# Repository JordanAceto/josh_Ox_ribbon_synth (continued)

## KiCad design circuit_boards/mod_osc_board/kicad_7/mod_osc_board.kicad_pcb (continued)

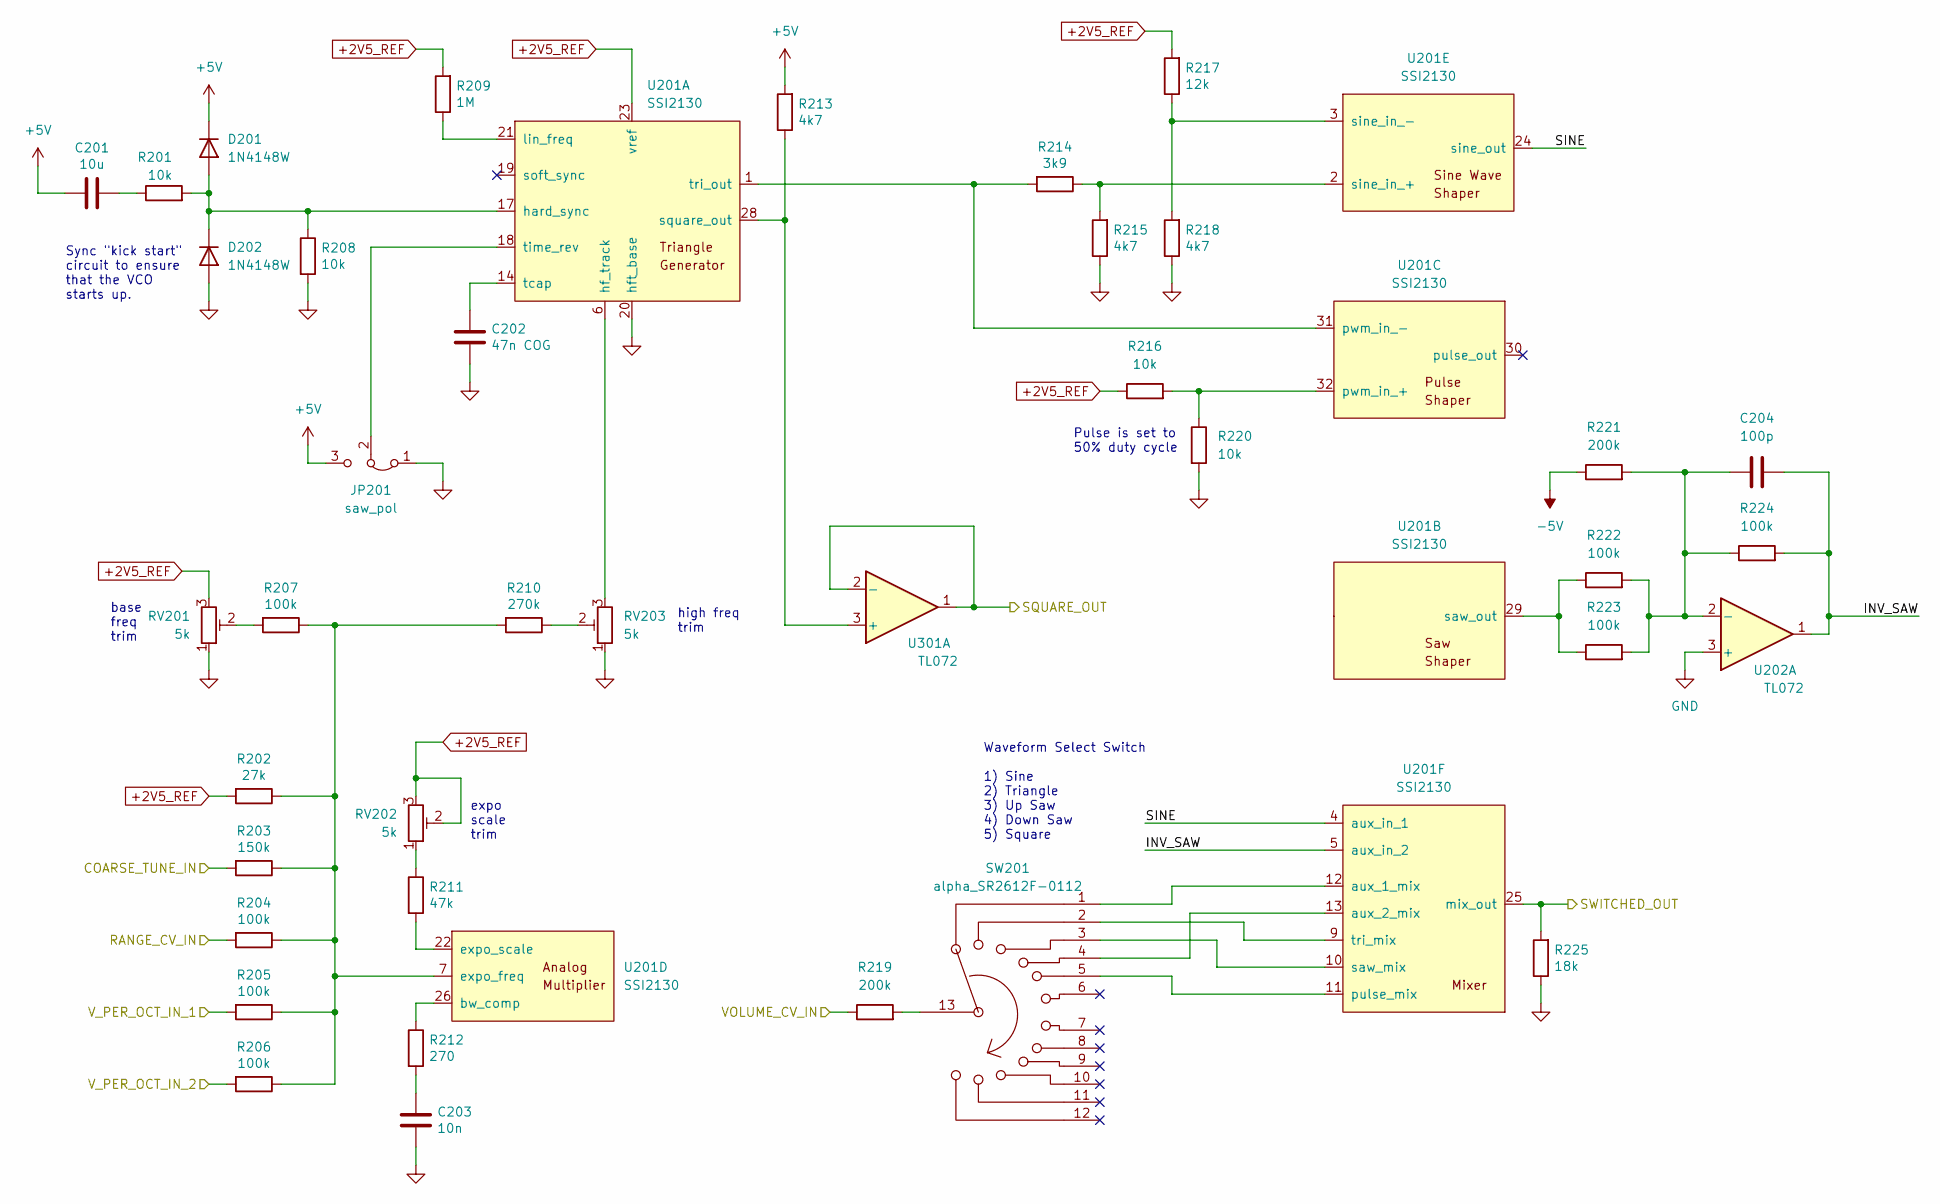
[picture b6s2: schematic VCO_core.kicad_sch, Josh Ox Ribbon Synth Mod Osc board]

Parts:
C201: 10u; C_0805_2012Metric
C202: 47n COG; C_0805_2012Metric
C203: 10n; C_0805_2012Metric
C204: 100p; C_0805_2012Metric
D201, D202: 1N4148W; D_SOD-123
JP201: saw_pol; SolderJumper-3_P1.3mm_Bridged12_RoundedPad1.0x1.5mm
R201, R208, R216, R220: 10k; R_0805_2012Metric
R202: 27k; R_0805_2012Metric
R203: 150k; R_0805_2012Metric
R204, R205, R206, R207, R222, R223, R224: 100k; R_0805_2012Metric
R209: 1M; R_0805_2012Metric
R210: 270k; R_0805_2012Metric
R211: 47k; R_0805_2012Metric
R212: 270; R_0805_2012Metric
R213, R215, R218: 4k7; R_0805_2012Metric
R214: 3k9; R_0805_2012Metric
R217: 12k; R_0805_2012Metric
R219, R221: 200k; R_0805_2012Metric
R225: 18k; R_0805_2012Metric
RV201, RV202, RV203: 5k; Potentiometer_Bourns_3296W_Vertical
SW201: alpha_SR2612F-0112; apha_SR2612F-0112
U201: SSI2130; PQN32_HandSoldering
U202, U301: TL072; SO-8_5.3x6.2mm_P1.27mm

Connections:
+2V5_REF: R202.2, R209.2, R216.1, R217.2, RV201.3, RV202.2, RV202.3, U201.23 (vref); also elsewhere on the board
+5V: C201.2, D201.1 (K), JP201.3 (B), R213.2; also elsewhere on the board
-5V: R221.1; also elsewhere on the board
/VCO_core/COARSE_TUNE_IN: R203.2; also elsewhere on the board
/VCO_core/INV_SAW: C204.2, R224.2, U201.5 (aux_in_2), U202.1
/VCO_core/RANGE_CV_IN: R204.2; also elsewhere on the board
/VCO_core/SINE: U201.4 (aux_in_1), U201.24 (sine_out)
/VCO_core/SQUARE_OUT: U301.1, U301.2 (-); also elsewhere on the board
/VCO_core/SWITCHED_OUT: R225.2, U201.25 (mix_out); also elsewhere on the board
/VCO_core/VOLUME_CV_IN: R219.1; also elsewhere on the board
/VCO_core/V_PER_OCT_IN_1: R205.2; also elsewhere on the board
/VCO_core/V_PER_OCT_IN_2: R206.2; also elsewhere on the board
unnamed: C201.1, R201.1
unnamed: C203.1, R212.2
unnamed: D201.2 (A), D202.1 (K), R201.2, R208.1, U201.17 (hard_sync)
unnamed: JP201.2 (C), U201.18 (time_rev)
unnamed: R207.2, RV201.2
unnamed: R210.1, RV203.2
unnamed: R211.1, RV202.1
unnamed: R219.2, SW201.13
unnamed: RV203.3, U201.6 (hf_track)
unnamed: R209.1, U201.21 (lin_freq)
unnamed: R213.1, U201.28 (square_out), U301.3 (+)
unnamed: C202.1, U201.14 (tcap)
unnamed: R214.2, U201.1 (tri_out), U201.31 (pwm_in_-)
unnamed: R222.1, R223.1, U201.29 (saw_out)
unnamed: R216.2, R220.1, U201.32 (pwm_in_+)
unnamed: R212.1, U201.26 (bw_comp)
unnamed: R202.1, R203.1, R204.1, R205.1, R206.1, R207.1, R210.2, U201.7 (expo_freq)
unnamed: R211.2, U201.22 (expo_scale)
unnamed: R214.1, R215.2, U201.2 (sine_in_+)
unnamed: R217.1, R218.2, U201.3 (sine_in_-)
unnamed: SW201.1, U201.12 (aux_1_mix)
unnamed: SW201.4, U201.13 (aux_2_mix)
unnamed: SW201.5, U201.11 (pulse_mix)
unnamed: SW201.3, U201.10 (saw_mix)
unnamed: SW201.2, U201.9 (tri_mix)
unnamed: C204.1, R221.2, R222.2, R223.2, R224.1, U202.2 (-)

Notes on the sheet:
Waveform Select Switch 1) Sine 2) Triangle 3) Up Saw 4) Down Saw 5) Square
high freq trim
Pulse is set to 50% duty cycle
expo scale trim
Sync "kick start" circuit to ensure that the VCO starts up.
base freq trim

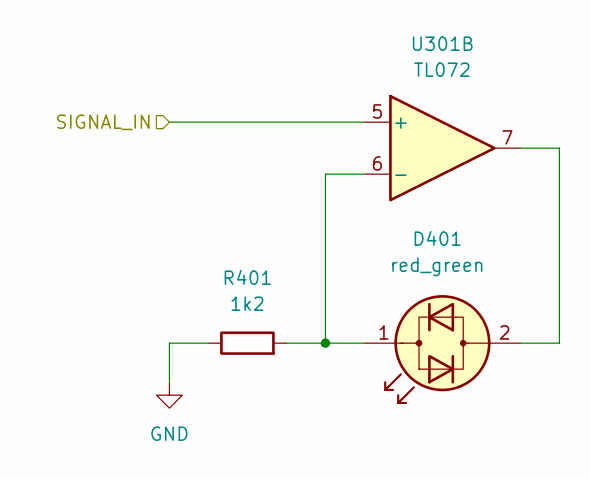
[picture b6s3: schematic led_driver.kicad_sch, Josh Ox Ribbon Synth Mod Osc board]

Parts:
D401: red_green; LED_D5.0mm
R401: 1k2; R_0805_2012Metric
U301: TL072; SO-8_5.3x6.2mm_P1.27mm

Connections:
/MOD_OSC_OUT: U301.5 (+); also elsewhere on the board
unnamed 19: D401.2 (AK), U301.7; also elsewhere on the board
unnamed 20: D401.1 (KA), R401.2, U301.6 (-); also elsewhere on the board

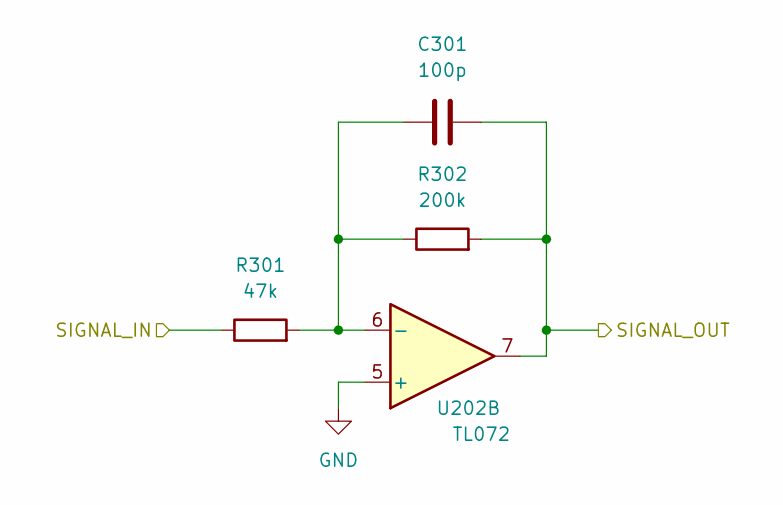
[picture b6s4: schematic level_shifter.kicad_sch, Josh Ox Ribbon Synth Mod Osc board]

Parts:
C301: 100p; C_0805_2012Metric
R301: 47k; R_0805_2012Metric
R302: 200k; R_0805_2012Metric
U202: TL072; SO-8_5.3x6.2mm_P1.27mm

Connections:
/MOD_OSC_OUT: C301.2, R302.2, U202.7; also elsewhere on the board
/VCO_core/SWITCHED_OUT: R301.1; also elsewhere on the board
unnamed: C301.1, R301.2, R302.1, U202.6 (-)

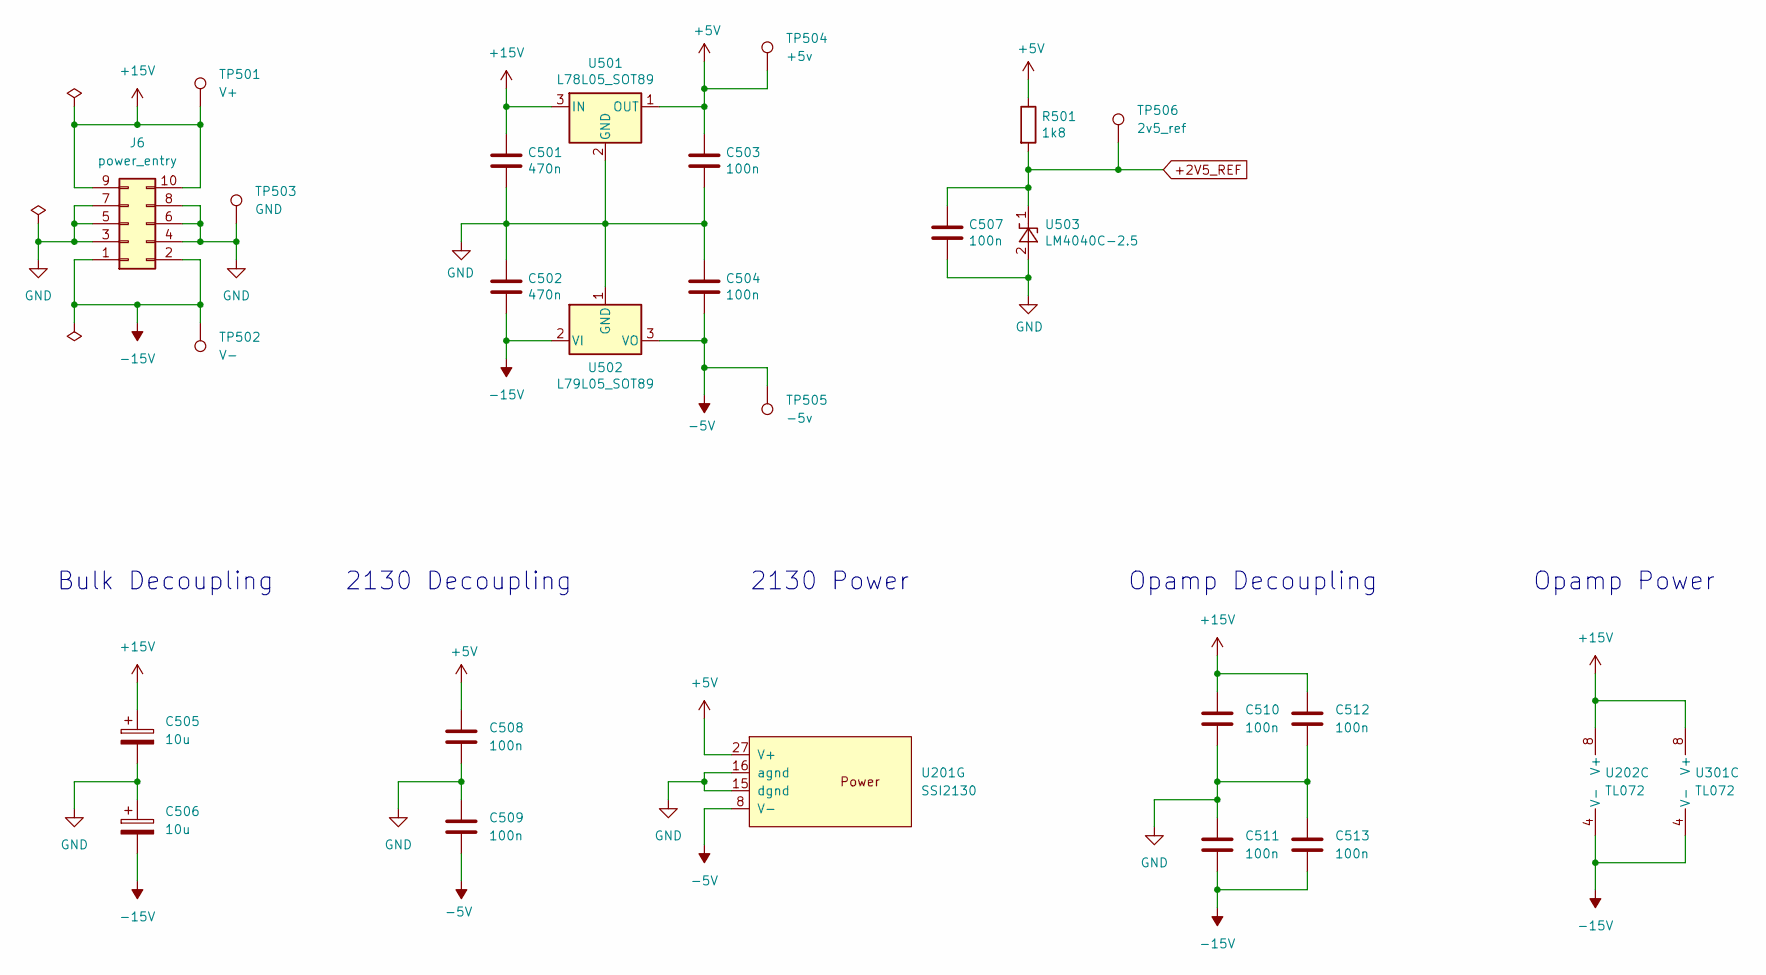
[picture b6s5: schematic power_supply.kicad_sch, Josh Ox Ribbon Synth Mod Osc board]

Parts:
C501, C502: 470n; C_0805_2012Metric
C503, C504, C507, C508, C509, C510, C511, C512, C513: 100n; C_0805_2012Metric
C505, C506: 10u; CP_Radial_D6.3mm_P2.50mm
J6: power_entry; IDC-Header_2x05_P2.54mm_Vertical
R501: 1k8; R_0805_2012Metric
TP501: V+; TestPoint_Keystone_5000-5004_Miniature
TP502: V-; TestPoint_Keystone_5000-5004_Miniature
TP503: GND; TestPoint_Bridge_Pitch7.62mm_Drill1.3mm
TP504: +5v; TestPoint_Keystone_5000-5004_Miniature
TP505: -5v; TestPoint_Keystone_5000-5004_Miniature
TP506: 2v5_ref; TestPoint_Keystone_5000-5004_Miniature
U201: SSI2130; PQN32_HandSoldering
U202, U301: TL072; SO-8_5.3x6.2mm_P1.27mm
U501: L78L05_SOT89; SOT-89-3
U502: L79L05_SOT89; SOT-89-3
U503: LM4040C-2.5; SOT-23

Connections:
+2V5_REF: C507.1, R501.2, TP506.1, U503.1 (K); also elsewhere on the board
+5V: C503.1, C508.1, R501.1, TP504.1, U201.27 (V+), U501.1 (OUT); also elsewhere on the board
+15V: C501.1, C505.1, C510.1, C512.1, J6.9, J6.10, TP501.1, U202.8 (V+), U301.8 (V+), U501.3 (IN)
-5V: C504.2, C509.2, TP505.1, U201.8 (V-), U502.3 (VO); also elsewhere on the board
-15V: C502.2, C506.2, C511.2, C513.2, J6.1, J6.2, TP502.1, U202.4 (V-), U301.4 (V-), U502.2 (VI)

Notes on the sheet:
2130 Decoupling
Opamp Decoupling
2130 Power
Opamp Power
Bulk Decoupling

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
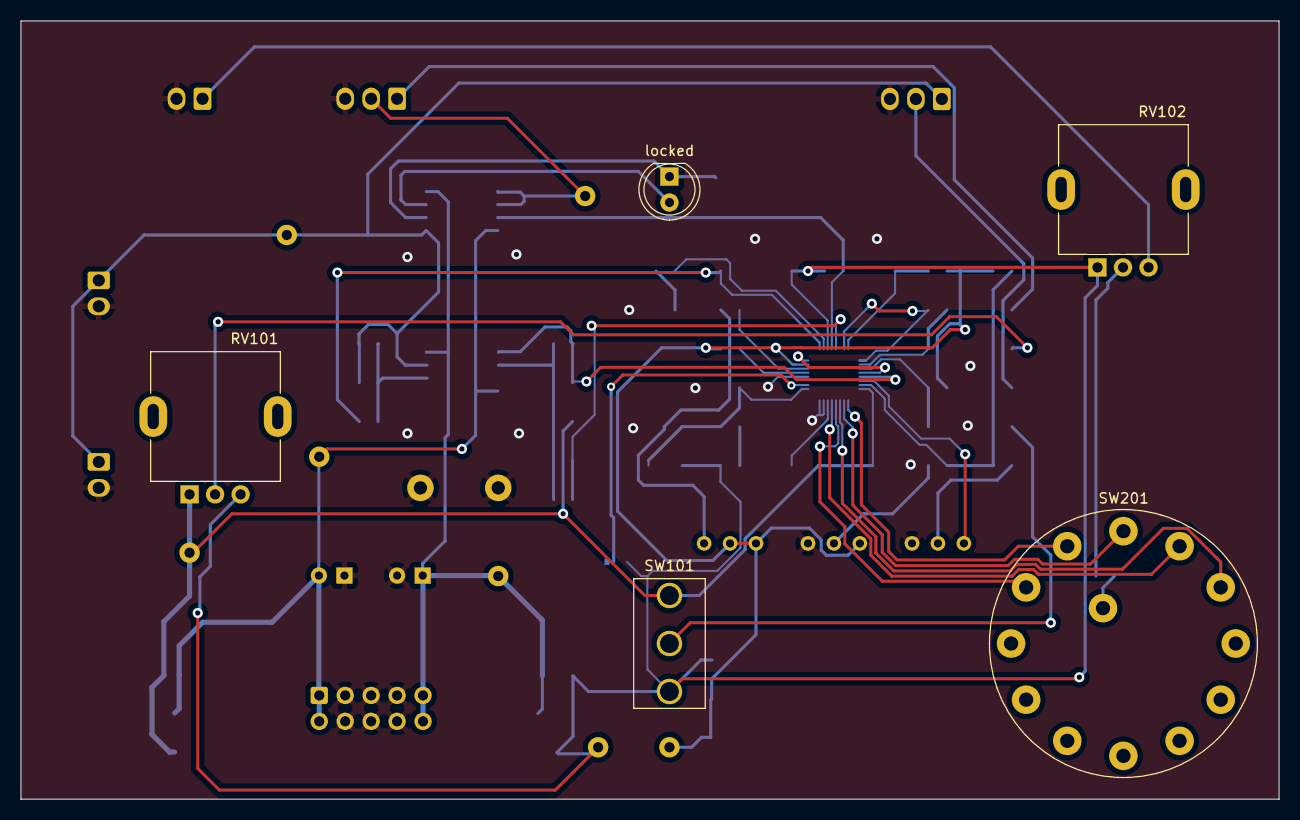
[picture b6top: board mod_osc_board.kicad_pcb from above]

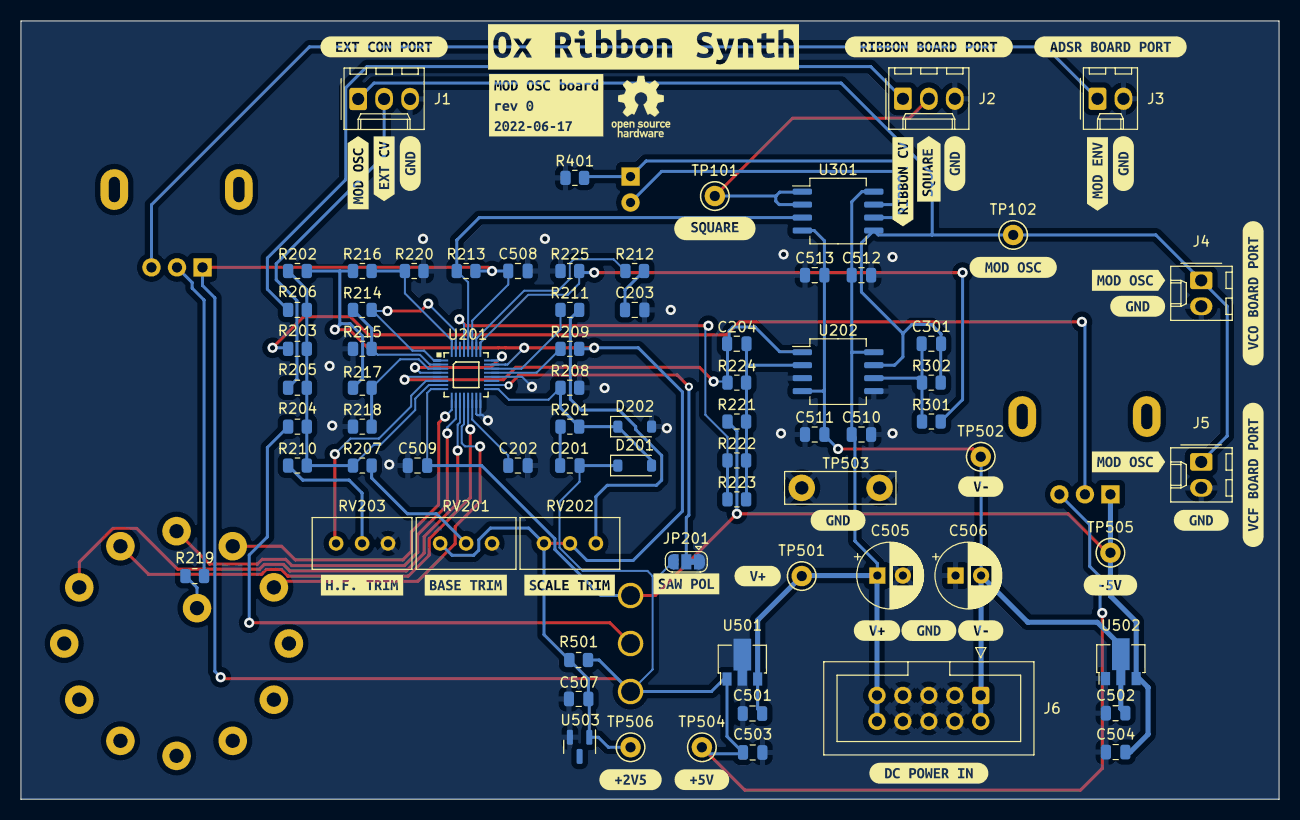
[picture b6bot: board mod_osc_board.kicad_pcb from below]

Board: 2 copper layers, 123.2 x 76.2 mm, 113 parts (108 on the bottom side), 46 nets.

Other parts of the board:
kibuzzard-62AC7A9F: G***; kibuzzard-62AC7A9F
kibuzzard-62AC7C76, kibuzzard-62AC7C76#2, kibuzzard-62AC7C76#3: G***; kibuzzard-62AC7C76
kibuzzard-62AC7CCE: G***; kibuzzard-62AC7CCE
kibuzzard-62AC7CEB: G***; kibuzzard-62AC7CEB
kibuzzard-62AC7D00: G***; kibuzzard-62AC7D00
kibuzzard-62AC7D1D: G***; kibuzzard-62AC7D1D
kibuzzard-62AC7D8B: G***; kibuzzard-62AC7D8B
kibuzzard-62AC7D30: G***; kibuzzard-62AC7D30
kibuzzard-62AC7D44: G***; kibuzzard-62AC7D44
kibuzzard-62AC7D55: G***; kibuzzard-62AC7D55
kibuzzard-62AC7D68: G***; kibuzzard-62AC7D68
kibuzzard-62AC7D79: G***; kibuzzard-62AC7D79
kibuzzard-62AC7DA9: G***; kibuzzard-62AC7DA9
kibuzzard-62AC7DB6: G***; kibuzzard-62AC7DB6
kibuzzard-62AC7DF7: G***; kibuzzard-62AC7DF7
kibuzzard-62AC7EA8: G***; kibuzzard-62AC7EA8
kibuzzard-62AC7EE1: G***; kibuzzard-62AC7EE1
kibuzzard-62AC7EFA: G***; kibuzzard-62AC7EFA
kibuzzard-62AC7F0B: G***; kibuzzard-62AC7F0B
kibuzzard-62AC78CB: G***; kibuzzard-62AC78CB
kibuzzard-62AC755C, kibuzzard-62AC755C#2, kibuzzard-62AC755C#3, kibuzzard-62AC755C#4, kibuzzard-62AC755C#5, kibuzzard-62AC755C#6, kibuzzard-62AC755C#7: G***; kibuzzard-62AC755C
kibuzzard-62AC791A, kibuzzard-62AC791A#2: G***; kibuzzard-62AC791A
kibuzzard-62AC792A, kibuzzard-62AC792A#2: G***; kibuzzard-62AC792A
kibuzzard-62AC911A: G***; kibuzzard-62AC911A
kibuzzard-62ACB089: G***; kibuzzard-62ACB089
locked: red_green; LED_D5.0mm

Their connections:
unnamed 19: locked.2 (AK); also elsewhere on the board
unnamed 20: locked.1 (KA); also elsewhere on the board

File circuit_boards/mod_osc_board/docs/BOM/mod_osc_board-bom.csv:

Row,Description,Part,References,Value,Footprint,Quantity Per PCB,Status,Datasheet
1,Unpolarized capacitor,C,C204 C301,100p,C_0805_2012Metric,2, ,~
2,Unpolarized capacitor,C,C203,10n,C_0805_2012Metric,1, ,~
3,Unpolarized capacitor,C,C202,47n COG,C_0805_2012Metric,1, ,~
4,Unpolarized capacitor,C,C503 C504 C507 C508 C509 C510 C511 C512 C513,100n,C_0805_2012Metric,9, ,~
5,Unpolarized capacitor,C,C501 C502,470n,C_0805_2012Metric,2, ,~
6,Unpolarized capacitor,C,C201,10u,C_0805_2012Metric,1, ,~
7,Polarized capacitor,C_Polarized,C505 C506,10u,CP_Radial_D6.3mm_P2.50mm,2, ,~
8,"75V 0.15A Fast Switching Diode, SOD-123",1N4148W,D201 D202,1N4148W,D_SOD-123,2, ,https://www.vishay.com/docs/85748/1n4148w.pdf
9,"Dual LED, bidirectional",LED_Dual_Bidirectional,D401,red_green,LED_D5.0mm,1, ,~
10,"Generic connector, single row, 01x02, script generated (kicad-library-utils/schlib/autogen/connector/)",Conn_01x02,J3 J4 J5,adsr_board_port,Molex_KK-254_AE-6410-02A_1x02_P2.54mm_Vertical,3, ,~
11,"Generic connector, single row, 01x03, script generated (kicad-library-utils/schlib/autogen/connector/)",Conn_01x03,J1 J2,ext_port,Molex_KK-254_AE-6410-03A_1x03_P2.54mm_Vertical,2, ,~
12,"Generic connector, double row, 02x05, odd/even pin numbering scheme (row 1 odd numbers, row 2 even numbers), script generated (kicad-library-utils/schlib/autogen/connector/)",Conn_02x05_Odd_Even,J6,power_entry,IDC-Header_2x05_P2.54mm_Vertical,1, ,~
13,Resistor,R,R212,270,R_0805_2012Metric,1, ,~
14,Resistor,R,R401,1k2,R_0805_2012Metric,1, ,~
15,Resistor,R,R501,1k8,R_0805_2012Metric,1, ,~
16,Resistor,R,R214,3k9,R_0805_2012Metric,1, ,~
17,Resistor,R,R213 R215 R218,4k7,R_0805_2012Metric,3, ,~
18,Resistor,R,R201 R208 R216 R220,10k,R_0805_2012Metric,4, ,~
19,Resistor,R,R217,12k,R_0805_2012Metric,1, ,~
20,Resistor,R,R225,18k,R_0805_2012Metric,1, ,~
21,Resistor,R,R202,27k,R_0805_2012Metric,1, ,~
22,Resistor,R,R211 R301,47k,R_0805_2012Metric,2, ,~
23,Resistor,R,R204 R205 R206 R207 R222 R223 R224,100k,R_0805_2012Metric,7, ,~
24,Resistor,R,R203,150k,R_0805_2012Metric,1, ,~
25,Resistor,R,R219 R221 R302,200k,R_0805_2012Metric,3, ,~
26,Resistor,R,R210,270k,R_0805_2012Metric,1, ,~
27,Resistor,R,R209,1M,R_0805_2012Metric,1, ,~
28,Trim-potentiometer,R_Potentiometer_Trim,RV201 RV202 RV203,5k,Potentiometer_Bourns_3296W_Vertical,3, ,~
29,Potentiometer,R_Potentiometer,RV101 RV102,10k,Potentiometer_P260T,2, ,~
30,"Switch, single pole double throw, center OFF position",SW_SPDT_MSM,SW101,SW_SPDT_MSM,SPDT_mini_toggle,1, ,~
31,rotary switch with 12 positions,alpha_SR2612F-0112,SW201,alpha_SR2612F-0112,apha_SR2612F-0112,1, ,http://www.taiwanalpha.com/downloads?target=products&id=229
32,"Positive 100mA 30V Linear Regulator, Fixed Output 5V, SOT-89",L78L05_SOT89,U501,L78L05_SOT89,SOT-89-3,1, ,http://www.st.com/content/ccc/resource/technical/document/da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
33,"Negative 100mA -30V Linear Regulator, Fixed Output -5V, SOT-89",L79L05_SOT89,U502,L79L05_SOT89,SOT-89-3,1, ,http://www.farnell.com/datasheets/1827870.pdf
34,"2.500V Precision Micropower Shunt Voltage Reference, SOT-23",LM4040DBZ-2.5,U503,LM4040C-2.5,SOT-23,1, ,http://www.ti.com/lit/ds/symlink/lm4040-n.pdf
35,,SSI2130,U201,SSI2130,PQN32_HandSoldering,1, ,
36,"Dual Low-Noise JFET-Input Operational Amplifiers, DIP-8/SOIC-8",TL072,U202 U301,TL072,SO-8_5.3x6.2mm_P1.27mm,2, ,http://www.ti.com/lit/ds/symlink/tl071.pdf





Project info:
Schematic:,mod_osc_board
Variant:,default
Revision:,0
Date:,2022-07-21
KiCad Version:,6.0.5+dfsg-1~bpo11+1
Statistics:
Component Groups:,36
Component Count:,69 (50 SMD/ 16 THT)
Fitted Components:,69 (50 SMD/ 16 THT)
Number of PCBs:,1
Total Components:,69

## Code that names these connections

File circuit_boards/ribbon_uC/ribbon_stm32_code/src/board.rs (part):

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    ),

    // ribbon gate output
    gate_pin: Pin<Output<PushPull>, L8, 'A', 5>,
}

impl Board {
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
        // gpio pins which are configured as analog inputs on the physical PCB
        let mut adc_pins = (
            gpioa.pa0.into_analog(&mut gpioa.moder, &mut gpioa.pupdr),
            gpioa.pa1.into_analog(&mut gpioa.moder, &mut gpioa.pupdr),
            gpioa.pa2.into_analog(&mut gpioa.moder, &mut gpioa.pupdr),
            gpioa.pa3.into_analog(&mut gpioa.moder, &mut gpioa.pupdr),
            gpioa.pa4.into_analog(&mut gpioa.moder, &mut gpioa.pupdr),
        );

        // configure DMA1 to transfer ADC readings to the buffer
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        }

        let tx_pin = gpioa
            .pa9
            .into_alternate(&mut gpioa.moder, &mut gpioa.otyper, &mut gpioa.afrh);
        let rx_pin =
            gpioa
                .pa10
                .into_alternate(&mut gpioa.moder, &mut gpioa.otyper, &mut gpioa.afrh);

        let usart = serial::Serial::usart1(
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        //
        ////////////////////////////////////////////////////////////////////////
        let sck = gpiob
            .pb3
            .into_alternate(&mut gpiob.moder, &mut gpiob.otyper, &mut gpiob.afrl);
        let sdi = gpiob
            .pb4
            .into_alternate(&mut gpiob.moder, &mut gpiob.otyper, &mut gpiob.afrl);
        let sdo = gpiob
            .pb5
            .into_alternate(&mut gpiob.moder, &mut gpiob.otyper, &mut gpiob.afrl);

        let nss = gpioa.pa15.into_push_pull_output_in_state(
            &mut gpioa.moder,
            &mut gpioa.otyper,
            PinState::High,
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        ////////////////////////////////////////////////////////////////////////
        let mode_switch = (
            gpiob
                .pb6
                .into_pull_up_input(&mut gpiob.moder, &mut gpiob.pupdr),
            gpiob
                .pb7
                .into_pull_up_input(&mut gpiob.moder, &mut gpiob.pupdr),
        );

        ////////////////////////////////////////////////////////////////////////
        //
        // Gate pin
        //
        ////////////////////////////////////////////////////////////////////////
        let gate_pin = gpioa
            .pa5
            .into_push_pull_output(&mut gpioa.moder, &mut gpioa.otyper);

        Self {
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            nss,
            delay,
            mode_switch,
            gate_pin,
        }
    }

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    /// `board.read_mode_switch()` is the enumerated state of the 3-way mode switch.
    pub fn read_mode_switch(&self) -> Switch3wayState {
        // The physical switch on the PCB is a SPDT on-off-on switch which grounds
        // either PB6, PB7, or neither pins depending on the position.
        match (self.mode_switch.0.is_low(), self.mode_switch.1.is_low()) {
            (false, true) => Switch3wayState::Up,
            (false, false) => Switch3wayState::Middle,
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        self.nss.set_high();
    }

    /// `board.set_gate(val)` sets the state of the gate pin to `val`.
    pub fn set_gate(&mut self, val: bool) {
        self.gate_pin.set_state(PinState::from(val));
    }

    /// `board.delay_ms(ms)` causes the board to busy-wait for `ms` milliseconds
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/// Pins which may be read by the ADC are represented here
#[derive(Clone, Copy)]
pub enum AdcPin {
    PA0 = 0,
    PA1 = 1,
    PA2 = 2,
    PA3 = 3,
    PA4 = 4,
}

/// Channels of the onboard DAC are represented here
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
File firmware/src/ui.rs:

use crate::board::{AdcPin, Board, Switch3wayState};

/// The user interface is represented here (i.e. the front panel pots and switches that the user interacts with)
pub struct UiState {
    pitch_mode: PitchMode,

    vco_lev: f32,
    modosc_lev: f32,
    vcf_lev: f32,
    delay_lev: f32,
}

/// There are three modes for the ribbon pitch information
#[derive(Clone, Copy)]
pub enum PitchMode {
    HardQuantize,
    Assist,
    Smooth,
}

/// Each main ribbon signal has its own attenuator
#[derive(Clone, Copy)]
pub enum LevelPot {
    Vco,
    ModOsc,
    Vcf,
    Delay,
}

impl UiState {
    /// `UiState::new()` is a new UI state initialized to default values.
    pub fn new() -> Self {
        Self {
            pitch_mode: PitchMode::Smooth,
            vco_lev: 0.0_f32,
            modosc_lev: 0.0_f32,
            vcf_lev: 0.0_f32,
            delay_lev: 0.0_f32,
        }
    }

    /// `ui.update()` updates the UI state by reading and storing the panel control user inputs.
    ///
    /// It is required to periodically call this function to updat the state of the UI controls. Since these controls
    /// are manually adjusted by the user, they don't need to be updated very fast, just fast enough that they don't
    /// feel sluggish to the user.
    pub fn update(&mut self, board: &mut Board) {
        self.pitch_mode = match board.read_mode_switch() {
            Switch3wayState::Up => PitchMode::HardQuantize,
            Switch3wayState::Middle => PitchMode::Assist,
            Switch3wayState::Down => PitchMode::Smooth,
        };

        // the level pots are center-detent so we can easily dial in exactly midway
        self.vco_lev = apply_midpoint_dead_zone(board.read_adc(AdcPin::PA3));
        self.modosc_lev = apply_midpoint_dead_zone(board.read_adc(AdcPin::PA2));
        self.vcf_lev = apply_midpoint_dead_zone(board.read_adc(AdcPin::PA1));
        self.delay_lev = apply_midpoint_dead_zone(board.read_adc(AdcPin::PA0))
    }

    /// `ui.attenuate(v, c)` scales the input value `v` by the position of the front panel potentiometer `c`
    ///
    /// # Arguments:
    ///
    /// * `val` - the value to scale
    ///
    /// * `control` - the enumerated panel control to scale the value with
    ///
    /// # Returns:
    ///
    /// * `val` attenuated by the given control. If the panel control is turned CCW then turn `val` down, if it's
    /// turned CW then turn `val` up.
    pub fn attenuate(&self, val: f32, control: LevelPot) -> f32 {
        match control {
            LevelPot::Vco => val * self.vco_lev,
            LevelPot::ModOsc => val * self.modosc_lev,
            LevelPot::Vcf => val * self.vcf_lev,
            LevelPot::Delay => val * self.delay_lev,
        }
    }

    /// `ui.pitch_mode()` is the current enumerated pitch mode, as set by the panel mount switch
    pub fn pitch_mode(&self) -> PitchMode {
        self.pitch_mode
    }
}

/// `apply_midpoint_dead_zone(v)` is the value `v` with a small dead zone in the center of the range
///
/// This means that for a small portion near the middle of the range changes will have no effect.
/// The is to make it easier to hit the midpoint of center-detent potiometers.
///
/// # Arguments:
///
/// * `val` - the value to apply dead zone to, must be in `[0.0, 1.0]`
fn apply_midpoint_dead_zone(val: f32) -> f32 {
    const DEAD_ZONE_WIDTH: f32 = 0.1_f32;
    const MIDPOINT: f32 = 0.5_f32;
    const DEAD_ZONE_START: f32 = MIDPOINT - DEAD_ZONE_WIDTH / 2.0_f32;
    const DEAD_ZONE_END: f32 = MIDPOINT + DEAD_ZONE_WIDTH / 2.0_f32;
    const SLOPE: f32 = MIDPOINT / DEAD_ZONE_START;

    if val < DEAD_ZONE_START {
        SLOPE * val
    } else if val <= DEAD_ZONE_END {
        // it's in the deadzone
        MIDPOINT
    } else {
        // it must be past the deadzone end
        SLOPE * (val - DEAD_ZONE_END) + MIDPOINT
    }
}

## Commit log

2018-12-15 initial commit, add adsr/pwm lfo board
2018-12-15 add mixer/vcf/vca board
2018-12-15 add modulation/ring mod board
2018-12-15 add ribbon board
2018-12-15 add sub osc board
2018-12-15 add vco board
2018-12-15 make pdf of adsr/pwm lfo board
2018-12-15 add pdf of mixer/vcf/vca board
2018-12-15 add pdf of modulation/ring mod board
2018-12-15 add pdf of sub osc board
2022-06-01 Add gitignore
2022-06-01 Begin big summer 22 refurb
2022-06-06 Progress on refurb boards, all incomplete and messy still
2022-06-09 Initial S&H board layout
2022-06-09 Initial VCF/VCA board layout
2022-06-09 Add block diagram for reference
2022-06-09 Change glide cap footprint, tweak silkscreen
2022-06-09 Tweak silkscreen
2022-06-11 Progress on ADSR board, need to decide between VC version or 555 version
2022-06-11 Initial ADSR board layout, 555 version
2022-06-12 Progress on modosc schematic
2022-06-12 Progress on ADSR layout
2022-06-13 Modosc schem progress
2022-06-14 Initial mod osc layout
2022-06-15 Add VCF base freq trimmers, tweak track widths
2022-06-15 Move some headers for better alignment
2022-06-15 Create pcb sandbox, for checking header alignment and such
2022-06-15 Update summer 22 refurb readme
2022-06-16 Progress on ribbon board
2022-06-16 Ribbon board progress, tidy up schem
2022-06-16 Rotate VCF mode switches
2022-06-17 Change directory structure, minor schem and pcb tweaks
2022-06-17 Add some details to pcb sandbox
2022-06-17 Add cool kibuzzard labels, minor tweaks
2022-06-17 Fix incorrect notch filter amp
2022-06-17 Fix rotation of separation pot, regenerate construction docs
2022-06-17 Buffer square, add saw polarity jumper
2022-06-18 Main VCO progress
2022-06-18 Progress on main VCO, schem getting close but not done
2022-06-18 Remove white/pink noise switch from VCO, use the one on the S&H board
2022-06-19 Main VCO rough parts placement
2022-06-20 Begin VCO pcb layout
2022-06-20 Initial VCO layout
2022-06-21 Fatten power traces on main VCO board
2022-06-21 Initial ribbon board layout
2022-06-26 Add .vscode files to gitignore
2022-06-26 Add KiBot doc gen files
2022-06-26 Update Modosc board
2022-06-26 Update ADSR board
2022-06-26 Update sample and hold board
2022-06-26 Update VCF/VCA board
2022-06-26 Update ribbon board
2022-06-26 Update VCO board
2022-06-26 Remove old S&H documentation
2022-06-26 Small VCO silkscreen changes
2022-06-26 Add power supply board
2022-06-28 Change some ADSR board values
2022-06-29 Start new panel
2022-06-30 Update KiBot files
2022-07-07 Change ADSR pot values
2022-07-08 Fix VCO issues, suboct switching, component values
2022-07-09 Update ribbon board values
2022-07-10 Add current draw markdown file
2022-07-10 Add ribbon assembly screw holes
2022-07-10 Major directory reorganization
2022-07-10 Update readmes
2022-07-10 Add panel README
2022-07-15 Remove copper pour underneath heatsinks
2022-07-15 Mounting holes to M4, trimmers in easier to reach spot
2022-07-16 Update version number
2022-07-16 Add prl backups to gitignore
2022-07-21 Update some S&H board values
2022-07-21 Update some VCF board values
2022-07-21 Update some mod-osc board values
2022-07-22 Add mains transformer wiring
2022-07-22 Add initial calibration instructions
2022-07-22 Fix calibration typo
2022-07-22 Add note about softpot
2022-07-22 Update mains transformer directory docs, add readme
2022-07-22 Update circuit boards readme, convert block diagram to png
2022-07-22 Add pcb documentation files
2022-07-23 Update ribbon span calibration instructions
2022-07-23 Increase noise gain in audio mixer
2022-07-23 Update mains input with current draw
2022-07-23 Increase linear FM gain on main VCO board
2022-07-23 Update main README
2022-07-25 Tweak ribbon values to improve note-on reliability
2022-07-25 Add license text
2022-08-10 Add PCB panel files
2022-08-11 Add to calibration instructions, how to remove bottom cover, add dividing lines
2022-08-11 Add individual circuit board READMEs
2022-08-11 Fix typo in ADSR README
2022-08-12 Add main VCO PCB kludges instructions
2022-08-14 Change VCA R for smoother volume knob action
2022-08-14 Change master volume pot to audio taper
2022-08-14 Fix ribbon schematic link
2022-08-14 Add pictures of finished synth, update main README
2022-08-24 Update README, add note about current status of the synth
2023-02-06 Upgrade ADSR board to new analog switch version
2023-02-06 Add analog delay to new VCF/VCA/BBD board
2023-02-06 Add new VCF/VCA/BBD Delay panel
2023-03-10 Begin to implement digital ribbon controller
2023-03-10 Add ribbon uC panel
2023-03-10 Change value of ribbon scaler R for 1v/oct trimming
2023-03-13 Improve ribbon behavior
2023-03-14 Implement glide, add slow timer for UI update scheduling
2023-03-14 Update digital ribbon README
2023-03-16 Change glide LPF for smoother knob action
2023-03-16 Make ribbon just pressed/released fns self clearing
2023-03-16 Implement basic MIDI transmitter, tweak quantizer, use DMA to send MIDI
2023-03-17 Use all-notes-off MIDI command
2023-03-17 Remove OR-1 in MIDI pitch bend
2023-03-17 Rename firmware dir
2023-03-17 Remove outdated ribbon board
2023-03-17 Add ribbon calibration image and steps
2023-03-17 Update current draw with new ribbon board
2023-03-17 Update ribbon firmware readme
2023-03-17 Add note about MIDI channel
2023-03-17 Remove old VCF/VCA board docs
2023-03-17 Remove old VCF/VCA board dirs
2023-03-17 Remove outdated ribbon calibration instructions
2023-03-25 Use midi-convert and midi-types crates instead of hand-rolled
2023-03-25 Only add samples to ribbon buff when finger is pressing
2023-03-25 Change how we write to DAC, now set Vout directly
2023-03-25 Change ribbon DAC scaling resistors for 10v max out
2023-03-26 Add MIDI receiver, quantizer now operates on voltages, remove MIDI transmitter code in main
2023-03-26 Move firmware to directory root
2023-03-26 Update firmware README
2023-03-26 Send MIDI mod-wheel on aux DAC channel
2023-03-26 Upgrade ADSR to analog swiitch version
2023-03-27 Change all pcbs and panels to KiCad 7, change docs structure
2023-03-27 Fix broken schematic links
2023-03-27 Bold ADSR sheet titles, use plotted ADSR schematic
2023-03-27 Add substance to firmware README
2023-04-06 Tweak portamento range and pot taper
2023-04-06 Remove debugger stuff
2023-04-06 Use is_empty instead of check for len == 0
2023-04-06 Use external synth-utils module
2023-04-07 Make upper ribbon R much bigger to mitigate noise issues
2023-04-07 Use glide processor from external repo, tweak glide time range
2023-04-08 Add docs for ribbon buffer protoboard
2023-04-08 Split license into hardware and software licenses
2023-04-08 Change calibration images to b&w, add BBD cal instructions
2023-04-08 Update front panel png
2023-04-12 New images with analog delay and quantized ribbon
2023-04-14 Use quantizer from remote repo, add fudge factor to make ribbon feel good
2023-04-14 Fix some clippy warnings in board module
2023-04-14 Use crate as dep instead of repo
2023-09-03 Ignore doc gen config files
2023-09-03 Change ribbon panel silkscreen GLIDE knob to DELAY knob
2023-09-03 Change ribbon GLIDE ctl to DELAY ctl on ribbon board
2023-09-03 Fix ribbon schematic font to match rest of schems
2023-09-03 Remove glide ctl and add ribbon delay ctl in firmware
2023-09-17 Fix outdated comments
